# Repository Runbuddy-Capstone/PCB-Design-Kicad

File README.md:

# PCB-Design-Kicad
This is all the files that are nessary to make the top of the board for our time logging system.  
THe pin header will run to the MAX3010X, ADXL335 on other boards.

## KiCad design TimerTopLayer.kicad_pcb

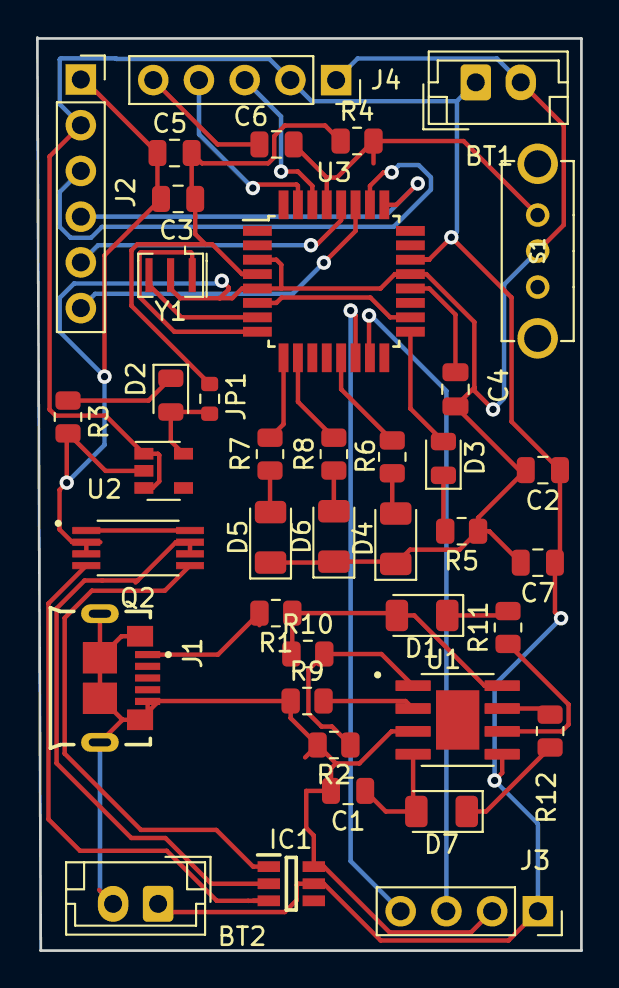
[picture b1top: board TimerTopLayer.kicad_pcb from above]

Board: 2 copper layers, 30.2 x 50.7 mm, 40 parts (0 on the bottom side), 38 nets.

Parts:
BT1, BT2: Battery; JST_EH_B2B-EH-A_1x02_P2.50mm_Vertical
C1, C2, C3, C7: 10uF; C_0805_2012Metric
C4, C5, C6: 0.1uF; C_0805_2012Metric
D1: Green; LED_1206_3216Metric
D2, D3: LED_Small; LED_0805_2012Metric
D4, D5, D6: LED; LED_1206_3216Metric
D7: RED; LED_1206_3216Metric
IC1: DW01; SOT95P280X135-6N
J1: USB3075-30-A; GCT_USB3075-30-A
J2: Conn_01x06_Male; PinSocket_1x06_P2.54mm_Vertical
J3: Conn_01x04_Male; PinSocket_1x04_P2.54mm_Vertical
J4: Conn_01x05_Male; PinSocket_1x05_P2.54mm_Vertical
JP1: Jumper_NC_Small; R_0603_1608Metric
Q2: FS8205A; SOP65P640X120-8N
R1: 1; R_0805_2012Metric
R2, R9, R10: UN; R_0805_2012Metric
R3, R4: 10K; R_0805_2012Metric
R5: 330; R_0805_2012Metric
R6, R7, R8: 20; R_0805_2012Metric
R11, R12: 1K; R_0805_2012Metric
S1: EG1213; SW_EG1213
U1: TP4056; SOP127P600X175-9N
U2: MIC5205-3.3YM5; SOT-23-5
U3: ATmega328P-AU; TQFP-32_7x7mm_P0.8mm
Y1: Resonator; Resonator_SMD_muRata_CSTxExxV-3Pin_3.0x1.1mm

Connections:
/3.7V: BT1.1, BT2.1, C2.1, C7.1, IC1.5, J2.2, J3.1, J4.2, U1.5, U2.1, U2.3, U3.22
/Pro-Mini/A2: J2.4, U3.25
/Pro-Mini/A3: J2.3, U3.26
/Pro-Mini/D5: R7.2, U3.9
/Pro-Mini/D6: R8.2, U3.10
/Pro-Mini/D9: R6.1, U3.13
/Pro-Mini/D10: J3.4, U3.14
/Pro-Mini/DTR: C6.2, J4.5
/Pro-Mini/MOSI-D11: J3.3, U3.15
/Pro-Mini/RXI: J4.3, U3.30
/Pro-Mini/SCK-D13: D3.2, U3.17
/Pro-Mini/TX0: J4.4, U3.31
/SCL: J2.6, U3.27
/SDA: J2.5, U3.28
/USBPowerIn/Gate1: IC1.1, Q2.5
/USBPowerIn/Gate2: IC1.3, Q2.4
/USBPowerIn/VBUS: C1.1, D1.2, D7.2, R1.1, R10.1, U1.4, U1.8
GND: BT1.2, BT2.2, C1.2, C2.2, C3.2, C4.2, C5.2, C7.2, D4.1, D5.1, D6.1, IC1.6, J1.5, J1.S1, J1.S2, J1.S3, J1.S4, J1.S5, J1.S6, J2.1, J3.2, J4.1, Q2.2, Q2.3, R2.2, R3.1, R5.1, R9.1, S1.2, U1.3, U2.2, U3.3, U3.5, U3.21, Y1.2
unnamed: C4.1, U3.20
unnamed: C6.1, R4.2, S1.3, U3.29
unnamed: D1.1, R11.2
unnamed: D2.1, R3.2
unnamed: D2.2, JP1.1, U2.5
unnamed: D3.1, R5.2
unnamed: D4.2, R6.2
unnamed: D5.2, R7.1
unnamed: D6.2, R8.1
unnamed: D7.1, R12.2
unnamed: IC1.2, Q2.6, Q2.7
unnamed: J1.1, R1.2
unnamed: Q2.1, Q2.8
unnamed: R9.2, U1.2
unnamed: R2.1, R10.2, U1.1
unnamed: R11.1, U1.6
unnamed: R12.1, U1.7
unnamed: U3.7, Y1.3
unnamed: U3.8, Y1.1
VCC: C3.1, C5.1, JP1.2, R4.1, U3.4, U3.6, U3.18
